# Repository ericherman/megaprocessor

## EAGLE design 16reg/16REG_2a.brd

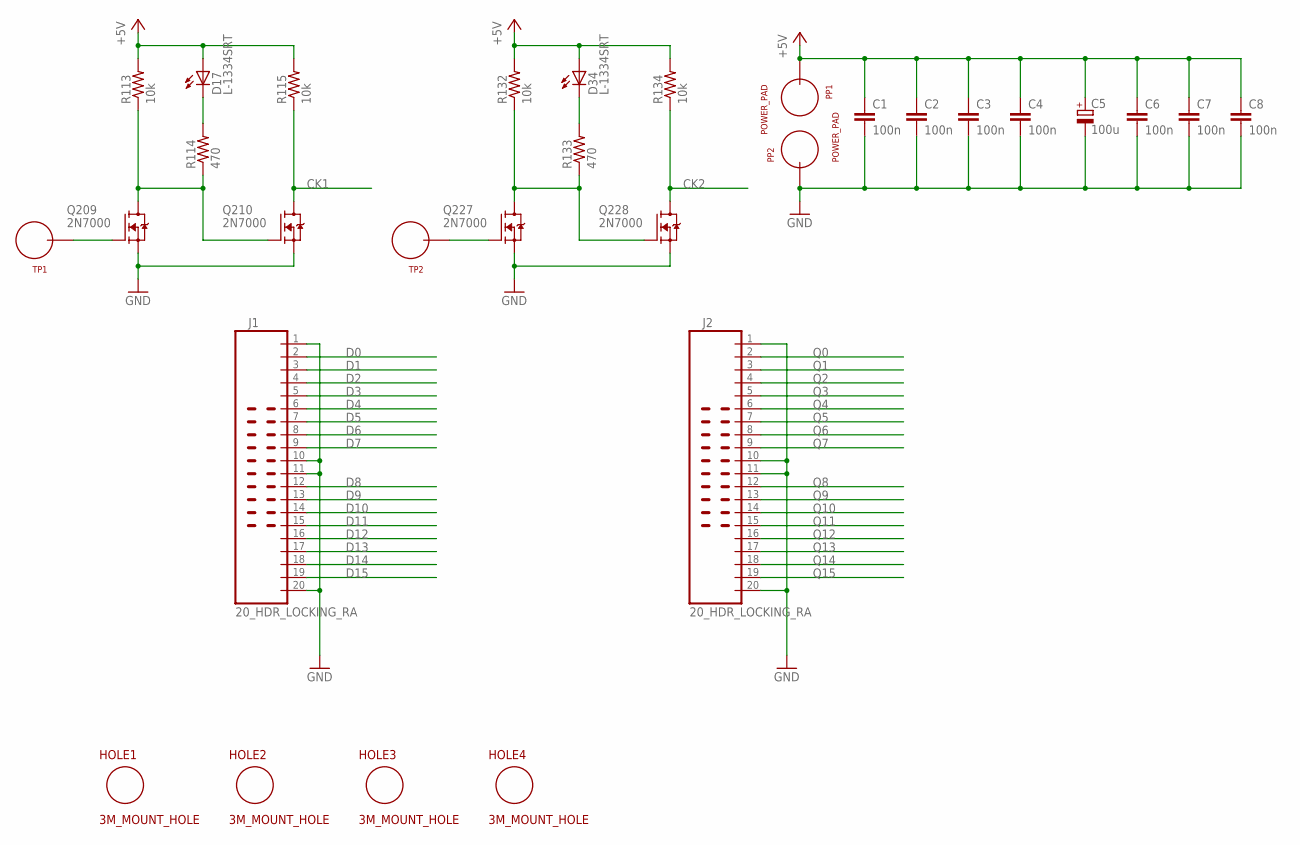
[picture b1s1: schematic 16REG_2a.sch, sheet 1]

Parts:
C1, C2, C3, C4, C6, C7, C8: 100n; CAP_P2INCH
C5: 100u; POLARISED_CAP_2P5
D17, D34: L-1334SRT; LED3MM
HOLE1, HOLE2, HOLE3, HOLE4: 3M_MOUNT_HOLE; 3M_HOLE
J1, J2: 20_HDR_LOCKING_RA
PP1, PP2: POWER_PAD
Q209, Q210, Q227, Q228: 2N7000; TO92-DGS
R113, R115, R132, R134: 10k; R_P2INCH
R114, R133: 470; R_P2INCH
TP1, TP2: TEST_LOOP

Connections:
+5V: C1.1, C2.1, C3.1, C4.1, C5.A, C6.1, C7.1, C8.1, D17.A, D34.A, PP1.1, R113.2, R115.2, R132.2, R134.2; also elsewhere on the board
CK1: Q210.D, R115.1; also elsewhere on the board
CK2: Q228.D, R134.1; also elsewhere on the board
D0: J1.2; also elsewhere on the board
D1: J1.3; also elsewhere on the board
D2: J1.4; also elsewhere on the board
D3: J1.5; also elsewhere on the board
D4: J1.6; also elsewhere on the board
D5: J1.7; also elsewhere on the board
D6: J1.8; also elsewhere on the board
D7: J1.9; also elsewhere on the board
D8: J1.12; also elsewhere on the board
D9: J1.13; also elsewhere on the board
D10: J1.14; also elsewhere on the board
D11: J1.15; also elsewhere on the board
D12: J1.16; also elsewhere on the board
D13: J1.17; also elsewhere on the board
D14: J1.18; also elsewhere on the board
D15: J1.19; also elsewhere on the board
GND: C1.2, C2.2, C3.2, C4.2, C5.K, C6.2, C7.2, C8.2, J1.1, J1.10, J1.11, J1.20, J2.1, J2.10, J2.11, J2.20, PP2.1, Q209.S, Q210.S, Q227.S, Q228.S; also elsewhere on the board
unnamed: Q227.G, TP2.P$1
unnamed: Q227.D, Q228.G, R132.1, R133.1
unnamed: D34.K (C), R133.2
unnamed: D17.K (C), R114.2
unnamed: Q209.G, TP1.P$1
unnamed: Q209.D, Q210.G, R113.1, R114.1
Q0: J2.2; also elsewhere on the board
Q1: J2.3; also elsewhere on the board
Q2: J2.4; also elsewhere on the board
Q3: J2.5; also elsewhere on the board
Q4: J2.6; also elsewhere on the board
Q5: J2.7; also elsewhere on the board
Q6: J2.8; also elsewhere on the board
Q7: J2.9; also elsewhere on the board
Q8: J2.12; also elsewhere on the board
Q9: J2.13; also elsewhere on the board
Q10: J2.14; also elsewhere on the board
Q11: J2.15; also elsewhere on the board
Q12: J2.16; also elsewhere on the board
Q13: J2.17; also elsewhere on the board
Q14: J2.18; also elsewhere on the board
Q15: J2.19; also elsewhere on the board

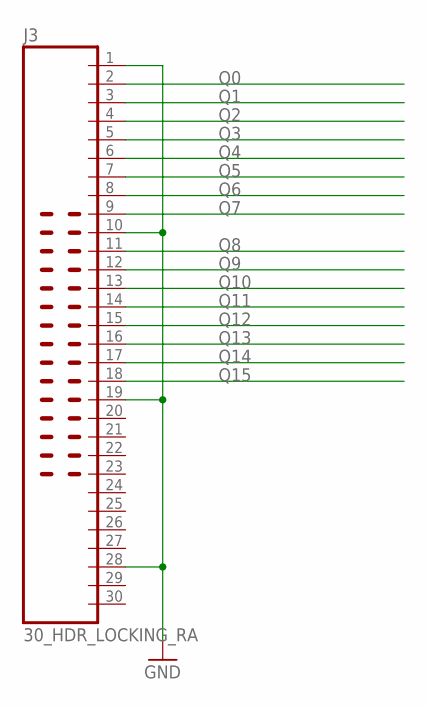
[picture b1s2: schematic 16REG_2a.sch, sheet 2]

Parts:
J3: 30_HDR_LOCKING_RA

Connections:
GND: J3.1, J3.10, J3.19, J3.28; also elsewhere on the board
Q0: J3.2; also elsewhere on the board
Q1: J3.3; also elsewhere on the board
Q2: J3.4; also elsewhere on the board
Q3: J3.5; also elsewhere on the board
Q4: J3.6; also elsewhere on the board
Q5: J3.7; also elsewhere on the board
Q6: J3.8; also elsewhere on the board
Q7: J3.9; also elsewhere on the board
Q8: J3.11; also elsewhere on the board
Q9: J3.12; also elsewhere on the board
Q10: J3.13; also elsewhere on the board
Q11: J3.14; also elsewhere on the board
Q12: J3.15; also elsewhere on the board
Q13: J3.16; also elsewhere on the board
Q14: J3.17; also elsewhere on the board
Q15: J3.18; also elsewhere on the board

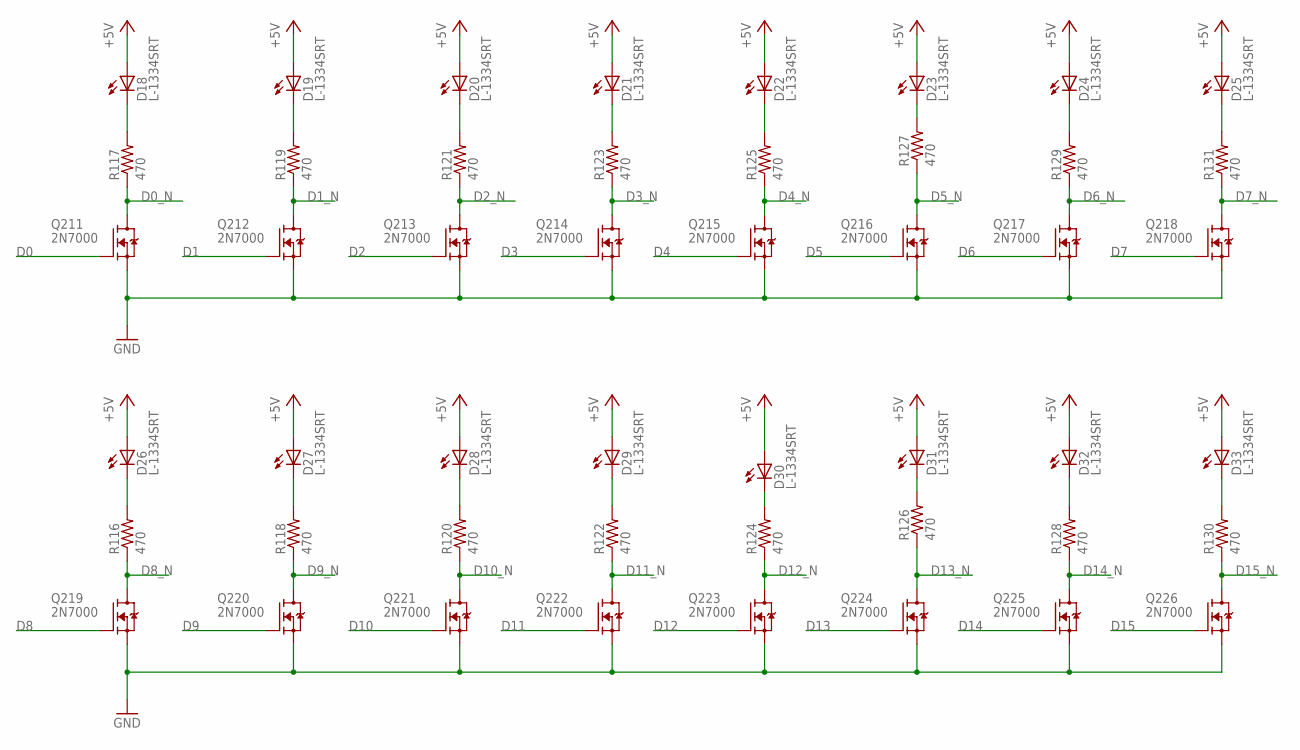
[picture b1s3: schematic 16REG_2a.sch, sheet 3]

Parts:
D18, D19, D20, D21, D22, D23, D24, D25, D26, D27, D28, D29, D30, D31, D32, D33: L-1334SRT; LED3MM
Q211, Q212, Q213, Q214, Q215, Q216, Q217, Q218, Q219, Q220, Q221, Q222, Q223, Q224, Q225, Q226: 2N7000; TO92-DGS
R116, R117, R118, R119, R120, R121, R122, R123, R124, R125, R126, R127, R128, R129, R130, R131: 470; R_P2INCH

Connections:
+5V: D18.A, D19.A, D20.A, D21.A, D22.A, D23.A, D24.A, D25.A, D26.A, D27.A, D28.A, D29.A, D30.A, D31.A, D32.A, D33.A; also elsewhere on the board
D0: Q211.G; also elsewhere on the board
D0_N: Q211.D, R117.1
D1: Q212.G; also elsewhere on the board
D1_N: Q212.D, R119.1
D2: Q213.G; also elsewhere on the board
D2_N: Q213.D, R121.1
D3: Q214.G; also elsewhere on the board
D3_N: Q214.D, R123.1
D4: Q215.G; also elsewhere on the board
D4_N: Q215.D, R125.1
D5: Q216.G; also elsewhere on the board
D5_N: Q216.D, R127.1
D6: Q217.G; also elsewhere on the board
D6_N: Q217.D, R129.1
D7: Q218.G; also elsewhere on the board
D7_N: Q218.D, R131.1
D8: Q219.G; also elsewhere on the board
D8_N: Q219.D, R116.1
D9: Q220.G; also elsewhere on the board
D9_N: Q220.D, R118.1
D10: Q221.G; also elsewhere on the board
D10_N: Q221.D, R120.1
D11: Q222.G; also elsewhere on the board
D11_N: Q222.D, R122.1
D12: Q223.G; also elsewhere on the board
D12_N: Q223.D, R124.1
D13: Q224.G; also elsewhere on the board
D13_N: Q224.D, R126.1
D14: Q225.G; also elsewhere on the board
D14_N: Q225.D, R128.1
D15: Q226.G; also elsewhere on the board
D15_N: Q226.D, R130.1
GND: Q211.S, Q212.S, Q213.S, Q214.S, Q215.S, Q216.S, Q217.S, Q218.S, Q219.S, Q220.S, Q221.S, Q222.S, Q223.S, Q224.S, Q225.S, Q226.S; also elsewhere on the board
unnamed: D18.K (C), R117.2
unnamed: D19.K (C), R119.2
unnamed: D20.K (C), R121.2
unnamed: D21.K (C), R123.2
unnamed: D22.K (C), R125.2
unnamed: D23.K (C), R127.2
unnamed: D24.K (C), R129.2
unnamed: D25.K (C), R131.2
unnamed: D33.K (C), R130.2
unnamed: D32.K (C), R128.2
unnamed: D31.K (C), R126.2
unnamed: D30.K (C), R124.2
unnamed: D29.K (C), R122.2
unnamed: D28.K (C), R120.2
unnamed: D27.K (C), R118.2
unnamed: D26.K (C), R116.2

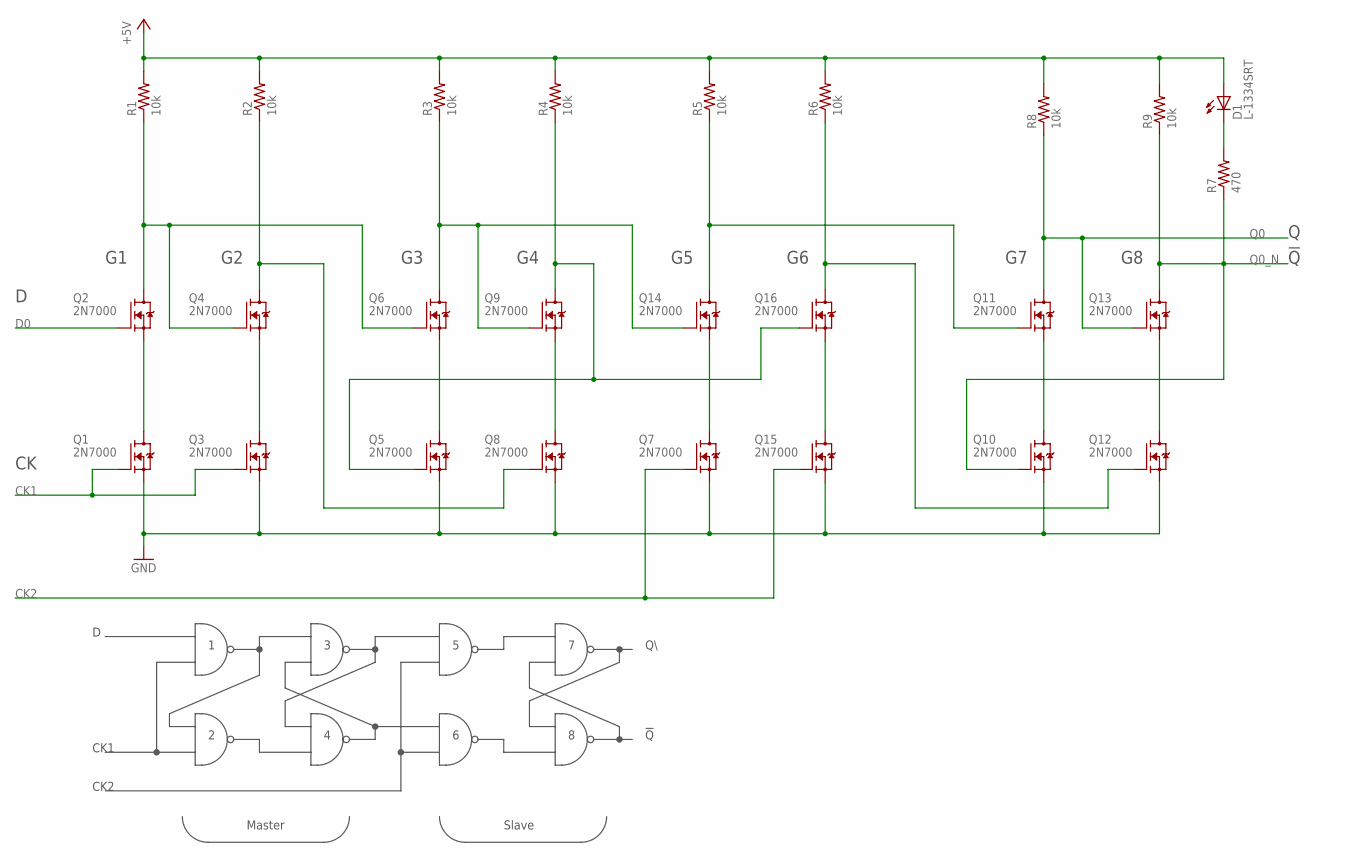
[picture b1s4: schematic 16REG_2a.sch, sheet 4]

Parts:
D1: L-1334SRT; LED3MM
Q1, Q2, Q3, Q4, Q5, Q6, Q7, Q8, Q9, Q10, Q11, Q12, Q13, Q14, Q15, Q16: 2N7000; TO92-DGS
R1, R2, R3, R4, R5, R6, R8, R9: 10k; R_P2INCH
R7: 470; R_P2INCH

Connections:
+5V: D1.A, R1.2, R2.2, R3.2, R4.2, R5.2, R6.2, R8.2, R9.2; also elsewhere on the board
CK1: Q1.G, Q3.G; also elsewhere on the board
CK2: Q7.G, Q15.G; also elsewhere on the board
D0: Q2.G; also elsewhere on the board
GND: Q1.S, Q3.S, Q5.S, Q7.S, Q8.S, Q10.S, Q12.S, Q15.S; also elsewhere on the board
unnamed: Q7.D, Q14.S
unnamed: Q6.D, Q9.G, Q14.G, R3.1
unnamed: Q15.D, Q16.S
unnamed: Q4.D, Q8.G, R2.1
unnamed: Q1.D, Q2.S
unnamed: Q3.D, Q4.S
unnamed: Q11.G, Q14.D, R5.1
unnamed: Q5.D, Q6.S
unnamed: Q8.D, Q9.S
unnamed: Q10.D, Q11.S
unnamed: Q12.D, Q13.S
unnamed: Q2.D, Q4.G, Q6.G, R1.1
unnamed: Q5.G, Q9.D, Q16.G, R4.1
unnamed: Q12.G, Q16.D, R6.1
unnamed: D1.K (C), R7.2
Q0: Q11.D, Q13.G, R8.1; also elsewhere on the board
Q0_N: Q10.G, Q13.D, R7.1, R9.1

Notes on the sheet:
CK1
CK2
Master
Slave

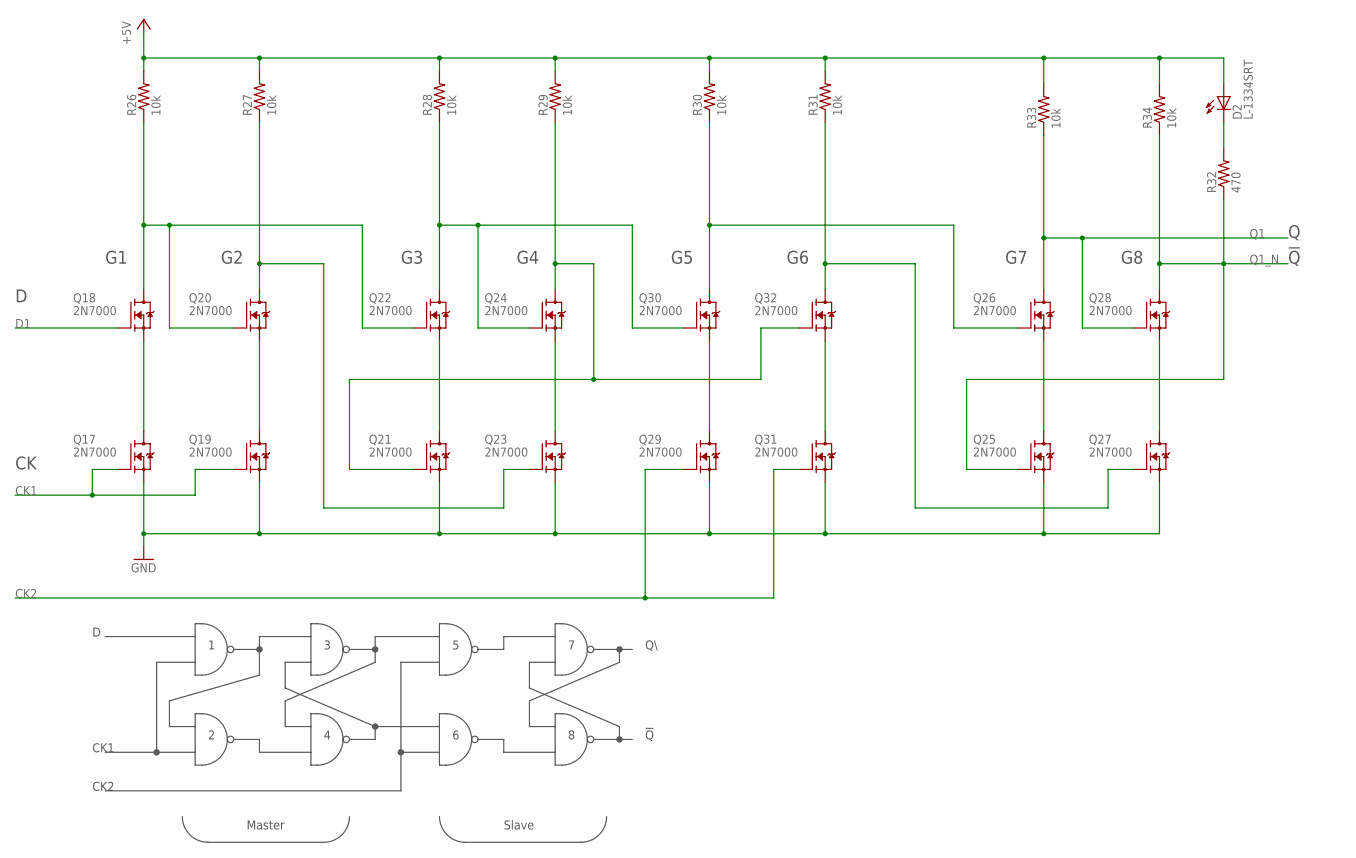
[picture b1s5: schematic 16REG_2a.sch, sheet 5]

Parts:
D2: L-1334SRT; LED3MM
Q17, Q18, Q19, Q20, Q21, Q22, Q23, Q24, Q25, Q26, Q27, Q28, Q29, Q30, Q31, Q32: 2N7000; TO92-DGS
R26, R27, R28, R29, R30, R31, R33, R34: 10k; R_P2INCH
R32: 470; R_P2INCH

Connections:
+5V: D2.A, R26.2, R27.2, R28.2, R29.2, R30.2, R31.2, R33.2, R34.2; also elsewhere on the board
CK1: Q17.G, Q19.G; also elsewhere on the board
CK2: Q29.G, Q31.G; also elsewhere on the board
D1: Q18.G; also elsewhere on the board
GND: Q17.S, Q19.S, Q21.S, Q23.S, Q25.S, Q27.S, Q29.S, Q31.S; also elsewhere on the board
unnamed: Q17.D, Q18.S
unnamed: Q19.D, Q20.S
unnamed: Q21.D, Q22.S
unnamed: Q23.D, Q24.S
unnamed: Q25.D, Q26.S
unnamed: Q27.D, Q28.S
unnamed: Q18.D, Q20.G, Q22.G, R26.1
unnamed: Q21.G, Q24.D, Q32.G, R29.1
unnamed: D2.K (C), R32.2
unnamed: Q22.D, Q24.G, Q30.G, R28.1
unnamed: Q20.D, Q23.G, R27.1
unnamed: Q29.D, Q30.S
unnamed: Q31.D, Q32.S
unnamed: Q26.G, Q30.D, R30.1
unnamed: Q27.G, Q32.D, R31.1
Q1: Q26.D, Q28.G, R33.1; also elsewhere on the board
Q1_N: Q25.G, Q28.D, R32.1, R34.1

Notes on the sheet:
CK1
CK2
Master
Slave

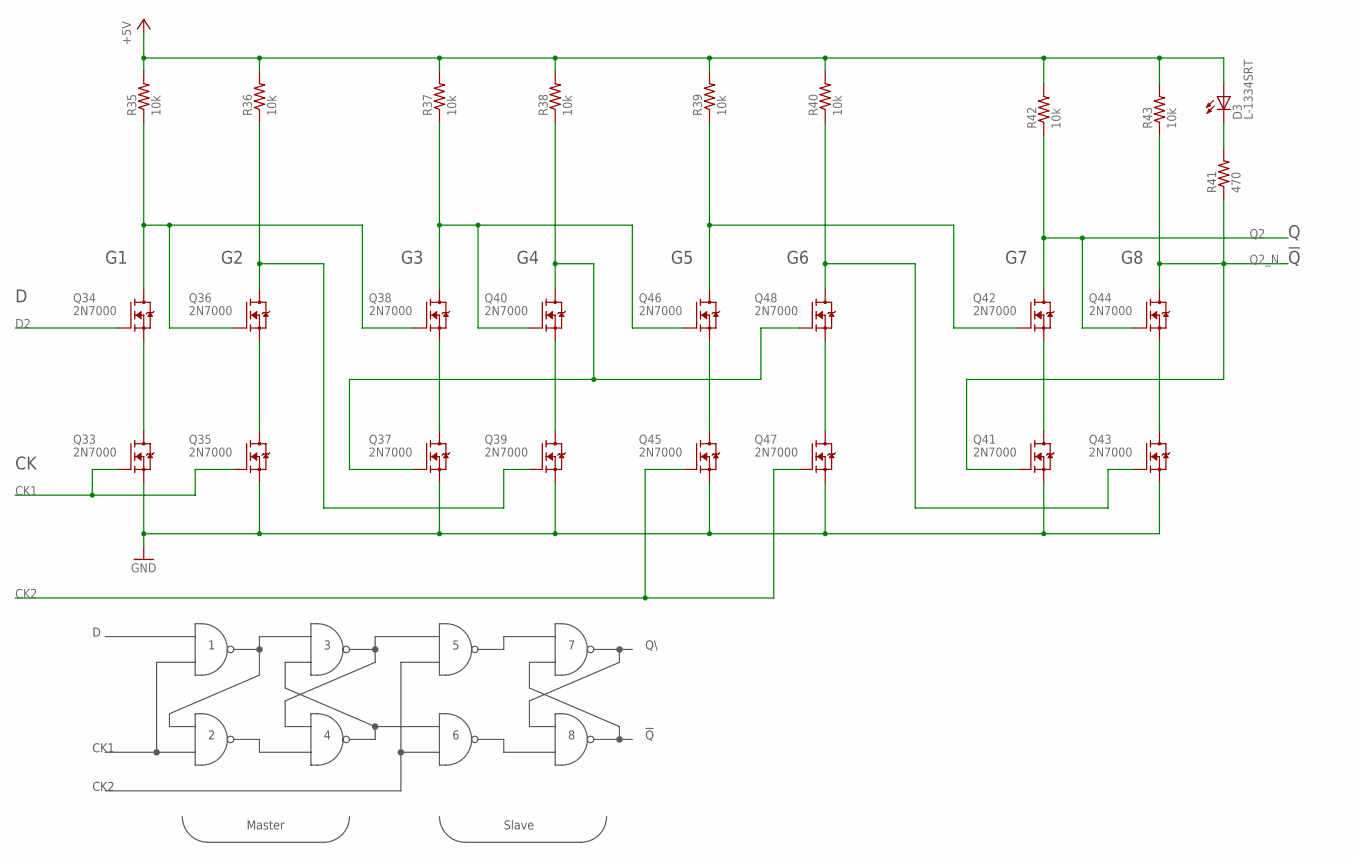
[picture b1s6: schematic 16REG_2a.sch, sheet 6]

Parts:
D3: L-1334SRT; LED3MM
Q33, Q34, Q35, Q36, Q37, Q38, Q39, Q40, Q41, Q42, Q43, Q44, Q45, Q46, Q47, Q48: 2N7000; TO92-DGS
R35, R36, R37, R38, R39, R40, R42, R43: 10k; R_P2INCH
R41: 470; R_P2INCH

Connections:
+5V: D3.A, R35.2, R36.2, R37.2, R38.2, R39.2, R40.2, R42.2, R43.2; also elsewhere on the board
CK1: Q33.G, Q35.G; also elsewhere on the board
CK2: Q45.G, Q47.G; also elsewhere on the board
D2: Q34.G; also elsewhere on the board
GND: Q33.S, Q35.S, Q37.S, Q39.S, Q41.S, Q43.S, Q45.S, Q47.S; also elsewhere on the board
unnamed: Q33.D, Q34.S
unnamed: Q35.D, Q36.S
unnamed: Q37.D, Q38.S
unnamed: Q39.D, Q40.S
unnamed: Q41.D, Q42.S
unnamed: Q43.D, Q44.S
unnamed: Q34.D, Q36.G, Q38.G, R35.1
unnamed: Q37.G, Q40.D, Q48.G, R38.1
unnamed: D3.K (C), R41.2
unnamed: Q38.D, Q40.G, Q46.G, R37.1
unnamed: Q36.D, Q39.G, R36.1
unnamed: Q45.D, Q46.S
unnamed: Q47.D, Q48.S
unnamed: Q42.G, Q46.D, R39.1
unnamed: Q43.G, Q48.D, R40.1
Q2: Q42.D, Q44.G, R42.1; also elsewhere on the board
Q2_N: Q41.G, Q44.D, R41.1, R43.1

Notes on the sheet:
CK1
CK2
Master
Slave

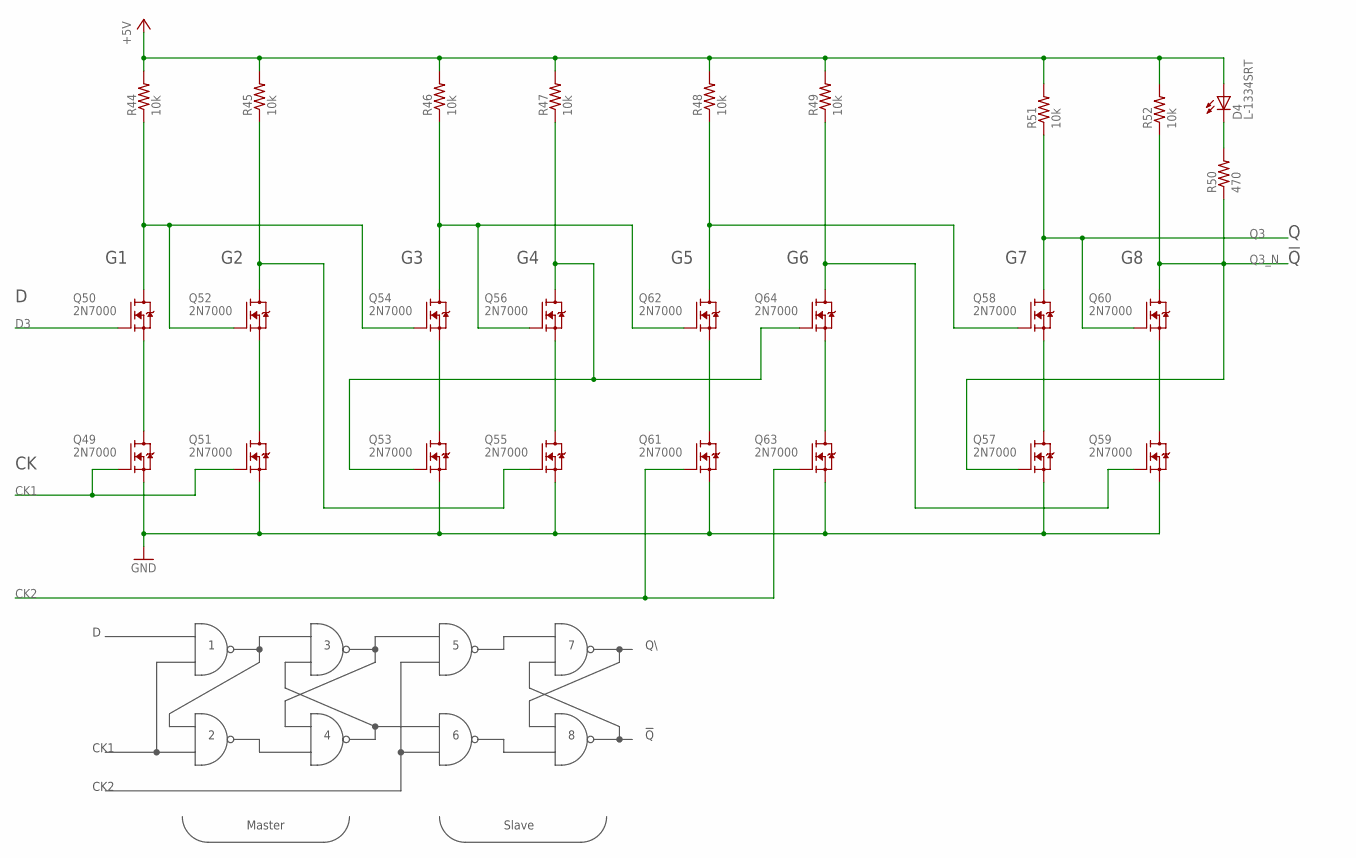
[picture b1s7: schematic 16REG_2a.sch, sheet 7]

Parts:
D4: L-1334SRT; LED3MM
Q49, Q50, Q51, Q52, Q53, Q54, Q55, Q56, Q57, Q58, Q59, Q60, Q61, Q62, Q63, Q64: 2N7000; TO92-DGS
R44, R45, R46, R47, R48, R49, R51, R52: 10k; R_P2INCH
R50: 470; R_P2INCH

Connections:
+5V: D4.A, R44.2, R45.2, R46.2, R47.2, R48.2, R49.2, R51.2, R52.2; also elsewhere on the board
CK1: Q49.G, Q51.G; also elsewhere on the board
CK2: Q61.G, Q63.G; also elsewhere on the board
D3: Q50.G; also elsewhere on the board
GND: Q49.S, Q51.S, Q53.S, Q55.S, Q57.S, Q59.S, Q61.S, Q63.S; also elsewhere on the board
unnamed: Q49.D, Q50.S
unnamed: Q51.D, Q52.S
unnamed: Q53.D, Q54.S
unnamed: Q55.D, Q56.S
unnamed: Q57.D, Q58.S
unnamed: Q59.D, Q60.S
unnamed: Q50.D, Q52.G, Q54.G, R44.1
unnamed: Q53.G, Q56.D, Q64.G, R47.1
unnamed: D4.K (C), R50.2
unnamed: Q54.D, Q56.G, Q62.G, R46.1
unnamed: Q52.D, Q55.G, R45.1
unnamed: Q61.D, Q62.S
unnamed: Q63.D, Q64.S
unnamed: Q58.G, Q62.D, R48.1
unnamed: Q59.G, Q64.D, R49.1
Q3: Q58.D, Q60.G, R51.1; also elsewhere on the board
Q3_N: Q57.G, Q60.D, R50.1, R52.1

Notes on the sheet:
CK1
CK2
Master
Slave

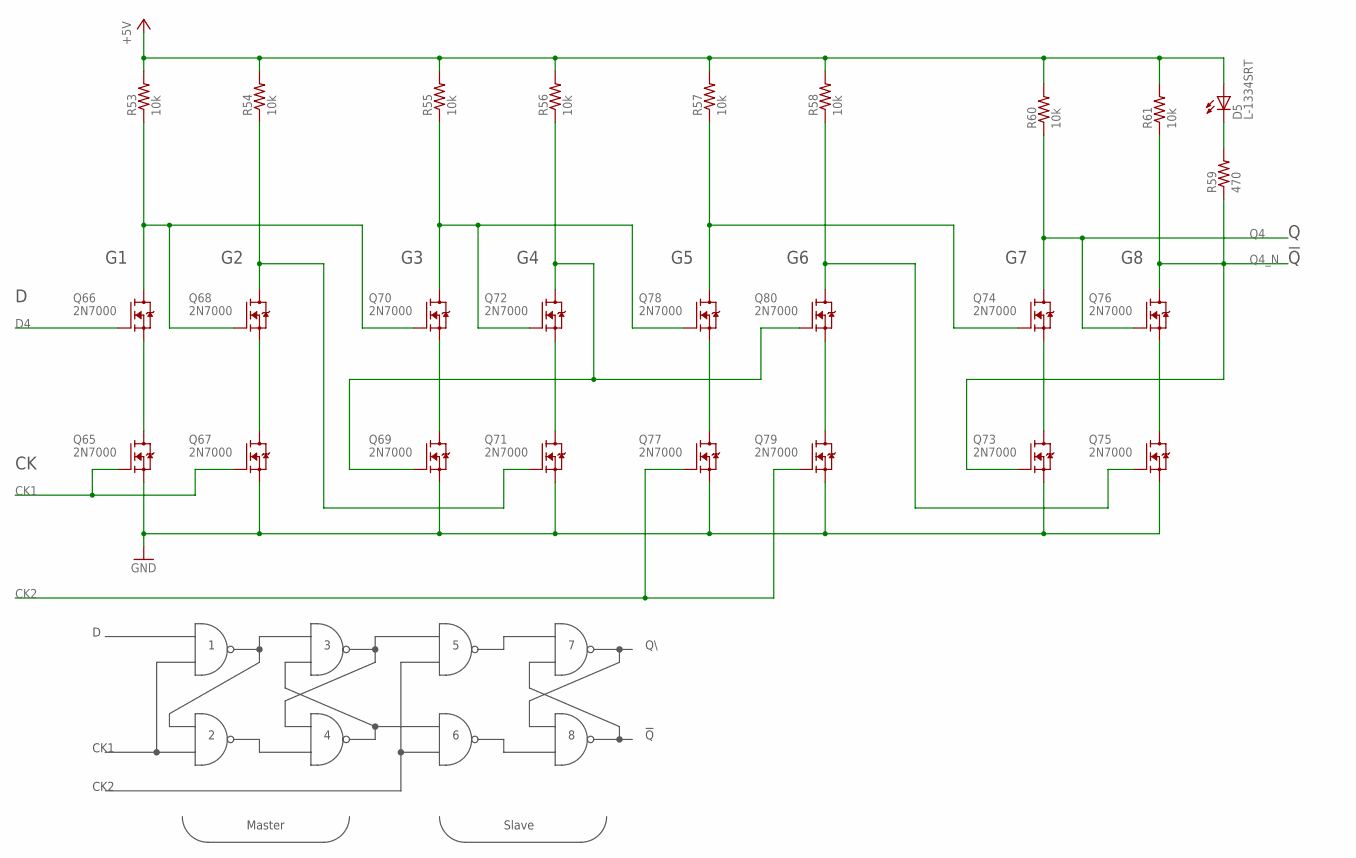
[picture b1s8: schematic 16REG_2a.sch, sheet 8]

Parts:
D5: L-1334SRT; LED3MM
Q65, Q66, Q67, Q68, Q69, Q70, Q71, Q72, Q73, Q74, Q75, Q76, Q77, Q78, Q79, Q80: 2N7000; TO92-DGS
R53, R54, R55, R56, R57, R58, R60, R61: 10k; R_P2INCH
R59: 470; R_P2INCH

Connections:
+5V: D5.A, R53.2, R54.2, R55.2, R56.2, R57.2, R58.2, R60.2, R61.2; also elsewhere on the board
CK1: Q65.G, Q67.G; also elsewhere on the board
CK2: Q77.G, Q79.G; also elsewhere on the board
D4: Q66.G; also elsewhere on the board
GND: Q65.S, Q67.S, Q69.S, Q71.S, Q73.S, Q75.S, Q77.S, Q79.S; also elsewhere on the board
unnamed: Q65.D, Q66.S
unnamed: Q67.D, Q68.S
unnamed: Q69.D, Q70.S
unnamed: Q71.D, Q72.S
unnamed: Q73.D, Q74.S
unnamed: Q75.D, Q76.S
unnamed: Q66.D, Q68.G, Q70.G, R53.1
unnamed: Q69.G, Q72.D, Q80.G, R56.1
unnamed: D5.K (C), R59.2
unnamed: Q70.D, Q72.G, Q78.G, R55.1
unnamed: Q68.D, Q71.G, R54.1
unnamed: Q77.D, Q78.S
unnamed: Q79.D, Q80.S
unnamed: Q74.G, Q78.D, R57.1
unnamed: Q75.G, Q80.D, R58.1
Q4: Q74.D, Q76.G, R60.1; also elsewhere on the board
Q4_N: Q73.G, Q76.D, R59.1, R61.1

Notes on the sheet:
CK1
CK2
Master
Slave

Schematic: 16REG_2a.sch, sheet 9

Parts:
D6: L-1334SRT; LED3MM
Q81, Q82, Q83, Q84, Q85, Q86, Q87, Q88, Q89, Q90, Q91, Q92, Q93, Q94, Q95, Q96: 2N7000; TO92-DGS
R62, R63, R64, R65, R66, R67, R69, R70: 10k; R_P2INCH
R68: 470; R_P2INCH

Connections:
+5V: D6.A, R62.2, R63.2, R64.2, R65.2, R66.2, R67.2, R69.2, R70.2; also elsewhere on the board
CK1: Q81.G, Q83.G; also elsewhere on the board
CK2: Q93.G, Q95.G; also elsewhere on the board
D5: Q82.G; also elsewhere on the board
GND: Q81.S, Q83.S, Q85.S, Q87.S, Q89.S, Q91.S, Q93.S, Q95.S; also elsewhere on the board
unnamed: Q81.D, Q82.S
unnamed: Q83.D, Q84.S
unnamed: Q85.D, Q86.S
unnamed: Q87.D, Q88.S
unnamed: Q89.D, Q90.S
unnamed: Q91.D, Q92.S
unnamed: Q82.D, Q84.G, Q86.G, R62.1
unnamed: Q85.G, Q88.D, Q96.G, R65.1
unnamed: D6.K (C), R68.2
unnamed: Q86.D, Q88.G, Q94.G, R64.1
unnamed: Q84.D, Q87.G, R63.1
unnamed: Q93.D, Q94.S
unnamed: Q95.D, Q96.S
unnamed: Q90.G, Q94.D, R66.1
unnamed: Q91.G, Q96.D, R67.1
Q5: Q90.D, Q92.G, R69.1; also elsewhere on the board
Q5_N: Q89.G, Q92.D, R68.1, R70.1

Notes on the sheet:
CK1
CK2
Master
Slave

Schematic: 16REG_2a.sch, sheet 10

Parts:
D7: L-1334SRT; LED3MM
Q97, Q98, Q99, Q100, Q101, Q102, Q103, Q104, Q105, Q106, Q107, Q108, Q109, Q110, Q111, Q112: 2N7000; TO92-DGS
R71, R72, R73, R74, R75, R76, R78, R79: 10k; R_P2INCH
R77: 470; R_P2INCH

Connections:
+5V: D7.A, R71.2, R72.2, R73.2, R74.2, R75.2, R76.2, R78.2, R79.2; also elsewhere on the board
CK1: Q97.G, Q99.G; also elsewhere on the board
CK2: Q109.G, Q111.G; also elsewhere on the board
D6: Q98.G; also elsewhere on the board
GND: Q97.S, Q99.S, Q101.S, Q103.S, Q105.S, Q107.S, Q109.S, Q111.S; also elsewhere on the board
unnamed: Q97.D, Q98.S
unnamed: Q99.D, Q100.S
unnamed: Q101.D, Q102.S
unnamed: Q103.D, Q104.S
unnamed: Q105.D, Q106.S
unnamed: Q107.D, Q108.S
unnamed: Q98.D, Q100.G, Q102.G, R71.1
unnamed: Q101.G, Q104.D, Q112.G, R74.1
unnamed: D7.K (C), R77.2
unnamed: Q102.D, Q104.G, Q110.G, R73.1
unnamed: Q100.D, Q103.G, R72.1
unnamed: Q109.D, Q110.S
unnamed: Q111.D, Q112.S
unnamed: Q106.G, Q110.D, R75.1
unnamed: Q107.G, Q112.D, R76.1
Q6: Q106.D, Q108.G, R78.1; also elsewhere on the board
Q6_N: Q105.G, Q108.D, R77.1, R79.1

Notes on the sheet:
CK1
CK2
Master
Slave

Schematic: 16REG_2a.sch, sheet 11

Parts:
D8: L-1334SRT; LED3MM
Q113, Q114, Q115, Q116, Q117, Q118, Q119, Q120, Q121, Q122, Q123, Q124, Q125, Q126, Q127, Q128: 2N7000; TO92-DGS
R80, R81, R82, R83, R84, R85, R87, R88: 10k; R_P2INCH
R86: 470; R_P2INCH

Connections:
+5V: D8.A, R80.2, R81.2, R82.2, R83.2, R84.2, R85.2, R87.2, R88.2; also elsewhere on the board
CK1: Q113.G, Q115.G; also elsewhere on the board
CK2: Q125.G, Q127.G; also elsewhere on the board
D7: Q114.G; also elsewhere on the board
GND: Q113.S, Q115.S, Q117.S, Q119.S, Q121.S, Q123.S, Q125.S, Q127.S; also elsewhere on the board
unnamed: Q113.D, Q114.S
unnamed: Q115.D, Q116.S
unnamed: Q117.D, Q118.S
unnamed: Q119.D, Q120.S
unnamed: Q121.D, Q122.S
unnamed: Q123.D, Q124.S
unnamed: Q114.D, Q116.G, Q118.G, R80.1
unnamed: Q117.G, Q120.D, Q128.G, R83.1
unnamed: D8.K (C), R86.2
unnamed: Q118.D, Q120.G, Q126.G, R82.1
unnamed: Q116.D, Q119.G, R81.1
unnamed: Q125.D, Q126.S
unnamed: Q127.D, Q128.S
unnamed: Q122.G, Q126.D, R84.1
unnamed: Q123.G, Q128.D, R85.1
Q7: Q122.D, Q124.G, R87.1; also elsewhere on the board
Q7_N: Q121.G, Q124.D, R86.1, R88.1

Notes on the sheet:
CK1
CK2
Master
Slave

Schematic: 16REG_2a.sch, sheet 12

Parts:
D9: L-1334SRT; LED3MM
Q129, Q130, Q131, Q132, Q133, Q134, Q135, Q136, Q137, Q138, Q139, Q140, Q141, Q142, Q143, Q144: 2N7000; TO92-DGS
R89, R90, R91, R92, R93, R94, R96, R97: 10k; R_P2INCH
R95: 470; R_P2INCH

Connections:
+5V: D9.A, R89.2, R90.2, R91.2, R92.2, R93.2, R94.2, R96.2, R97.2; also elsewhere on the board
CK1: Q129.G, Q131.G; also elsewhere on the board
CK2: Q141.G, Q143.G; also elsewhere on the board
D8: Q130.G; also elsewhere on the board
GND: Q129.S, Q131.S, Q133.S, Q135.S, Q137.S, Q139.S, Q141.S, Q143.S; also elsewhere on the board
unnamed: Q129.D, Q130.S
unnamed: Q131.D, Q132.S
unnamed: Q133.D, Q134.S
unnamed: Q135.D, Q136.S
unnamed: Q137.D, Q138.S
unnamed: Q139.D, Q140.S
unnamed: Q130.D, Q132.G, Q134.G, R89.1
unnamed: Q133.G, Q136.D, Q144.G, R92.1
unnamed: D9.K (C), R95.2
unnamed: Q134.D, Q136.G, Q142.G, R91.1
unnamed: Q132.D, Q135.G, R90.1
unnamed: Q141.D, Q142.S
unnamed: Q143.D, Q144.S
unnamed: Q138.G, Q142.D, R93.1
unnamed: Q139.G, Q144.D, R94.1
Q8: Q138.D, Q140.G, R96.1; also elsewhere on the board
Q8_N: Q137.G, Q140.D, R95.1, R97.1

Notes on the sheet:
CK1
CK2
Master
Slave

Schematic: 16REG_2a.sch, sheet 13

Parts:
D10: L-1334SRT; LED3MM
Q145, Q146, Q147, Q148, Q149, Q150, Q151, Q152, Q153, Q154, Q155, Q156, Q157, Q158, Q159, Q160: 2N7000; TO92-DGS
R98, R99, R100, R101, R102, R103, R105, R106: 10k; R_P2INCH
R104: 470; R_P2INCH

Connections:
+5V: D10.A, R98.2, R99.2, R100.2, R101.2, R102.2, R103.2, R105.2, R106.2; also elsewhere on the board
CK1: Q145.G, Q147.G; also elsewhere on the board
CK2: Q157.G, Q159.G; also elsewhere on the board
D9: Q146.G; also elsewhere on the board
GND: Q145.S, Q147.S, Q149.S, Q151.S, Q153.S, Q155.S, Q157.S, Q159.S; also elsewhere on the board
unnamed: Q145.D, Q146.S
unnamed: Q147.D, Q148.S
unnamed: Q149.D, Q150.S
unnamed: Q151.D, Q152.S
unnamed: Q153.D, Q154.S
unnamed: Q155.D, Q156.S
unnamed: Q146.D, Q148.G, Q150.G, R98.1
unnamed: Q149.G, Q152.D, Q160.G, R101.1
unnamed: D10.K (C), R104.2
unnamed: Q150.D, Q152.G, Q158.G, R100.1
unnamed: Q148.D, Q151.G, R99.1
unnamed: Q157.D, Q158.S
unnamed: Q159.D, Q160.S
unnamed: Q154.G, Q158.D, R102.1
unnamed: Q155.G, Q160.D, R103.1
Q9: Q154.D, Q156.G, R105.1; also elsewhere on the board
Q9_N: Q153.G, Q156.D, R104.1, R106.1

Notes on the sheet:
CK1
CK2
Master
Slave

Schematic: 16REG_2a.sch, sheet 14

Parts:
D11: L-1334SRT; LED3MM
Q161, Q162, Q163, Q164, Q165, Q166, Q167, Q168, Q169, Q170, Q171, Q172, Q173, Q174, Q175, Q176: 2N7000; TO92-DGS
R107, R108, R109, R110, R111, R112, R136, R137: 10k; R_P2INCH
R135: 470; R_P2INCH

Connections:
+5V: D11.A, R107.2, R108.2, R109.2, R110.2, R111.2, R112.2, R136.2, R137.2; also elsewhere on the board
CK1: Q161.G, Q163.G; also elsewhere on the board
CK2: Q173.G, Q175.G; also elsewhere on the board
D10: Q162.G; also elsewhere on the board
GND: Q161.S, Q163.S, Q165.S, Q167.S, Q169.S, Q171.S, Q173.S, Q175.S; also elsewhere on the board
unnamed: Q161.D, Q162.S
unnamed: Q163.D, Q164.S
unnamed: Q165.D, Q166.S
unnamed: Q167.D, Q168.S
unnamed: Q169.D, Q170.S
unnamed: Q171.D, Q172.S
unnamed: Q162.D, Q164.G, Q166.G, R107.1
unnamed: Q165.G, Q168.D, Q176.G, R110.1
unnamed: D11.K (C), R135.2
unnamed: Q166.D, Q168.G, Q174.G, R109.1
unnamed: Q164.D, Q167.G, R108.1
unnamed: Q173.D, Q174.S
unnamed: Q175.D, Q176.S
unnamed: Q170.G, Q174.D, R111.1
unnamed: Q171.G, Q176.D, R112.1
Q10: Q170.D, Q172.G, R136.1; also elsewhere on the board
Q10_N: Q169.G, Q172.D, R135.1, R137.1

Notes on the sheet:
CK1
CK2
Master
Slave

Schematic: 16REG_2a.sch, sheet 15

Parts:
D12: L-1334SRT; LED3MM
Q177, Q178, Q179, Q180, Q181, Q182, Q183, Q184, Q185, Q186, Q187, Q188, Q189, Q190, Q191, Q192: 2N7000; TO92-DGS
R138, R139, R140, R141, R142, R143, R145, R146: 10k; R_P2INCH
R144: 470; R_P2INCH

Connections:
+5V: D12.A, R138.2, R139.2, R140.2, R141.2, R142.2, R143.2, R145.2, R146.2; also elsewhere on the board
CK1: Q177.G, Q179.G; also elsewhere on the board
CK2: Q189.G, Q191.G; also elsewhere on the board
D11: Q178.G; also elsewhere on the board
GND: Q177.S, Q179.S, Q181.S, Q183.S, Q185.S, Q187.S, Q189.S, Q191.S; also elsewhere on the board
unnamed: Q177.D, Q178.S
unnamed: Q179.D, Q180.S
unnamed: Q181.D, Q182.S
unnamed: Q183.D, Q184.S
unnamed: Q185.D, Q186.S
unnamed: Q187.D, Q188.S
unnamed: Q178.D, Q180.G, Q182.G, R138.1
unnamed: Q181.G, Q184.D, Q192.G, R141.1
unnamed: D12.K (C), R144.2
unnamed: Q182.D, Q184.G, Q190.G, R140.1
unnamed: Q180.D, Q183.G, R139.1
unnamed: Q189.D, Q190.S
unnamed: Q191.D, Q192.S
unnamed: Q186.G, Q190.D, R142.1
unnamed: Q187.G, Q192.D, R143.1
Q11: Q186.D, Q188.G, R145.1; also elsewhere on the board
Q11_N: Q185.G, Q188.D, R144.1, R146.1

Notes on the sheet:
CK1
CK2
Master
Slave

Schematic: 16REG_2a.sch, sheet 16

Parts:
D13: L-1334SRT; LED3MM
Q193, Q194, Q195, Q196, Q197, Q198, Q199, Q200, Q201, Q202, Q203, Q204, Q205, Q206, Q207, Q208: 2N7000; TO92-DGS
R147, R148, R149, R150, R151, R152, R154, R155: 10k; R_P2INCH
R153: 470; R_P2INCH

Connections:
+5V: D13.A, R147.2, R148.2, R149.2, R150.2, R151.2, R152.2, R154.2, R155.2; also elsewhere on the board
CK1: Q193.G, Q195.G; also elsewhere on the board
CK2: Q205.G, Q207.G; also elsewhere on the board
D12: Q194.G; also elsewhere on the board
GND: Q193.S, Q195.S, Q197.S, Q199.S, Q201.S, Q203.S, Q205.S, Q207.S; also elsewhere on the board
unnamed: Q193.D, Q194.S
unnamed: Q195.D, Q196.S
unnamed: Q197.D, Q198.S
unnamed: Q199.D, Q200.S
unnamed: Q201.D, Q202.S
unnamed: Q203.D, Q204.S
unnamed: Q194.D, Q196.G, Q198.G, R147.1
unnamed: Q197.G, Q200.D, Q208.G, R150.1
unnamed: D13.K (C), R153.2
unnamed: Q198.D, Q200.G, Q206.G, R149.1
unnamed: Q196.D, Q199.G, R148.1
unnamed: Q205.D, Q206.S
unnamed: Q207.D, Q208.S
unnamed: Q202.G, Q206.D, R151.1
unnamed: Q203.G, Q208.D, R152.1
Q12: Q202.D, Q204.G, R154.1; also elsewhere on the board
Q12_N: Q201.G, Q204.D, R153.1, R155.1

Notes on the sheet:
CK1
CK2
Master
Slave

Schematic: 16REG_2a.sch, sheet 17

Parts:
D14: L-1334SRT; LED3MM
Q229, Q230, Q231, Q232, Q233, Q234, Q235, Q236, Q237, Q238, Q239, Q240, Q241, Q242, Q243, Q244: 2N7000; TO92-DGS
R156, R157, R158, R159, R160, R161, R163, R164: 10k; R_P2INCH
R162: 470; R_P2INCH

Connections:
+5V: D14.A, R156.2, R157.2, R158.2, R159.2, R160.2, R161.2, R163.2, R164.2; also elsewhere on the board
CK1: Q229.G, Q231.G; also elsewhere on the board
CK2: Q241.G, Q243.G; also elsewhere on the board
D13: Q230.G; also elsewhere on the board
GND: Q229.S, Q231.S, Q233.S, Q235.S, Q237.S, Q239.S, Q241.S, Q243.S; also elsewhere on the board
unnamed: Q229.D, Q230.S
unnamed: Q231.D, Q232.S
unnamed: Q233.D, Q234.S
unnamed: Q235.D, Q236.S
unnamed: Q237.D, Q238.S
unnamed: Q239.D, Q240.S
unnamed: Q230.D, Q232.G, Q234.G, R156.1
unnamed: Q233.G, Q236.D, Q244.G, R159.1
unnamed: D14.K (C), R162.2
unnamed: Q234.D, Q236.G, Q242.G, R158.1
unnamed: Q232.D, Q235.G, R157.1
unnamed: Q241.D, Q242.S
unnamed: Q243.D, Q244.S
unnamed: Q238.G, Q242.D, R160.1
unnamed: Q239.G, Q244.D, R161.1
Q13: Q238.D, Q240.G, R163.1; also elsewhere on the board
Q13_N: Q237.G, Q240.D, R162.1, R164.1

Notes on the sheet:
CK1
CK2
Master
Slave

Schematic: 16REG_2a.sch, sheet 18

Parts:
D15: L-1334SRT; LED3MM
Q245, Q246, Q247, Q248, Q249, Q250, Q251, Q252, Q253, Q254, Q255, Q256, Q257, Q258, Q259, Q260: 2N7000; TO92-DGS
R165, R166, R167, R168, R169, R170, R172, R173: 10k; R_P2INCH
R171: 470; R_P2INCH

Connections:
+5V: D15.A, R165.2, R166.2, R167.2, R168.2, R169.2, R170.2, R172.2, R173.2; also elsewhere on the board
CK1: Q245.G, Q247.G; also elsewhere on the board
CK2: Q257.G, Q259.G; also elsewhere on the board
D14: Q246.G; also elsewhere on the board
GND: Q245.S, Q247.S, Q249.S, Q251.S, Q253.S, Q255.S, Q257.S, Q259.S; also elsewhere on the board
unnamed: Q245.D, Q246.S
unnamed: Q247.D, Q248.S
unnamed: Q249.D, Q250.S
unnamed: Q251.D, Q252.S
unnamed: Q253.D, Q254.S
unnamed: Q255.D, Q256.S
unnamed: Q246.D, Q248.G, Q250.G, R165.1
unnamed: Q249.G, Q252.D, Q260.G, R168.1
unnamed: D15.K (C), R171.2
unnamed: Q250.D, Q252.G, Q258.G, R167.1
unnamed: Q248.D, Q251.G, R166.1
unnamed: Q257.D, Q258.S
unnamed: Q259.D, Q260.S
unnamed: Q254.G, Q258.D, R169.1
unnamed: Q255.G, Q260.D, R170.1
Q14: Q254.D, Q256.G, R172.1; also elsewhere on the board
Q14_N: Q253.G, Q256.D, R171.1, R173.1

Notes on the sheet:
CK1
CK2
Master
Slave

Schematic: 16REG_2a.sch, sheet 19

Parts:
D16: L-1334SRT; LED3MM
Q261, Q262, Q263, Q264, Q265, Q266, Q267, Q268, Q269, Q270, Q271, Q272, Q273, Q274, Q275, Q276: 2N7000; TO92-DGS
R174, R175, R176, R177, R178, R179, R181, R182: 10k; R_P2INCH
R180: 470; R_P2INCH

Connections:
+5V: D16.A, R174.2, R175.2, R176.2, R177.2, R178.2, R179.2, R181.2, R182.2; also elsewhere on the board
CK1: Q261.G, Q263.G; also elsewhere on the board
CK2: Q273.G, Q275.G; also elsewhere on the board
D15: Q262.G; also elsewhere on the board
GND: Q261.S, Q263.S, Q265.S, Q267.S, Q269.S, Q271.S, Q273.S, Q275.S; also elsewhere on the board
unnamed: Q261.D, Q262.S
unnamed: Q263.D, Q264.S
unnamed: Q265.D, Q266.S
unnamed: Q267.D, Q268.S
unnamed: Q269.D, Q270.S
unnamed: Q271.D, Q272.S
unnamed: Q262.D, Q264.G, Q266.G, R174.1
unnamed: Q265.G, Q268.D, Q276.G, R177.1
unnamed: D16.K (C), R180.2
unnamed: Q266.D, Q268.G, Q274.G, R176.1
unnamed: Q264.D, Q267.G, R175.1
unnamed: Q273.D, Q274.S
unnamed: Q275.D, Q276.S
unnamed: Q270.G, Q274.D, R178.1
unnamed: Q271.G, Q276.D, R179.1
Q15: Q270.D, Q272.G, R181.1; also elsewhere on the board
Q15_N: Q269.G, Q272.D, R180.1, R182.1

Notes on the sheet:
CK1
CK2
Master
Slave

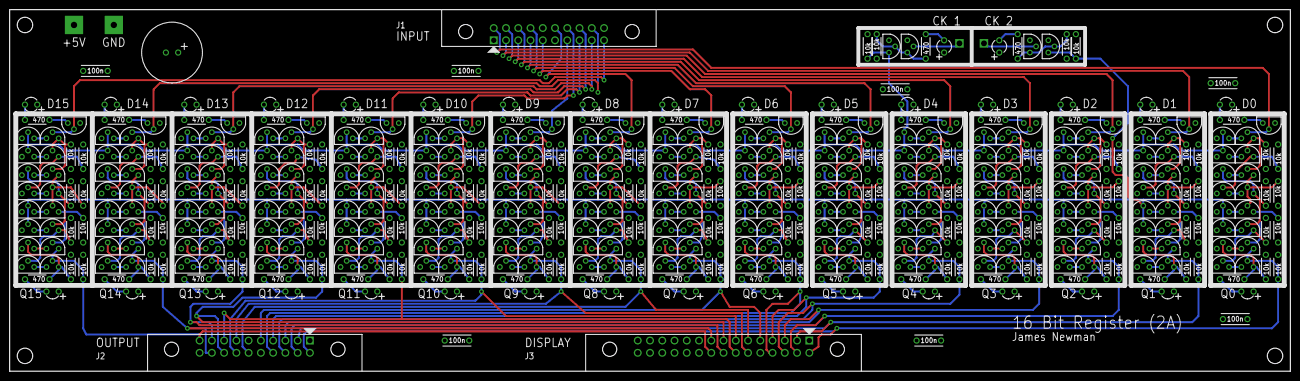
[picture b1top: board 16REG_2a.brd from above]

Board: 4 copper layers, 265.4 x 74.9 mm, 495 parts (0 on the bottom side), 330 nets.
